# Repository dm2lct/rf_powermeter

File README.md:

# rf_powermeter
This is a try to build a rf powermeter for vhf and uhf frequencies. 
It should work with any directional coupler you attach on it. 
Currently I'm still working on it so it should not be rebuilt. 
When I have built and programmed it I will update this repository with the software. 
 
a vhf/uhf swr/powermeter

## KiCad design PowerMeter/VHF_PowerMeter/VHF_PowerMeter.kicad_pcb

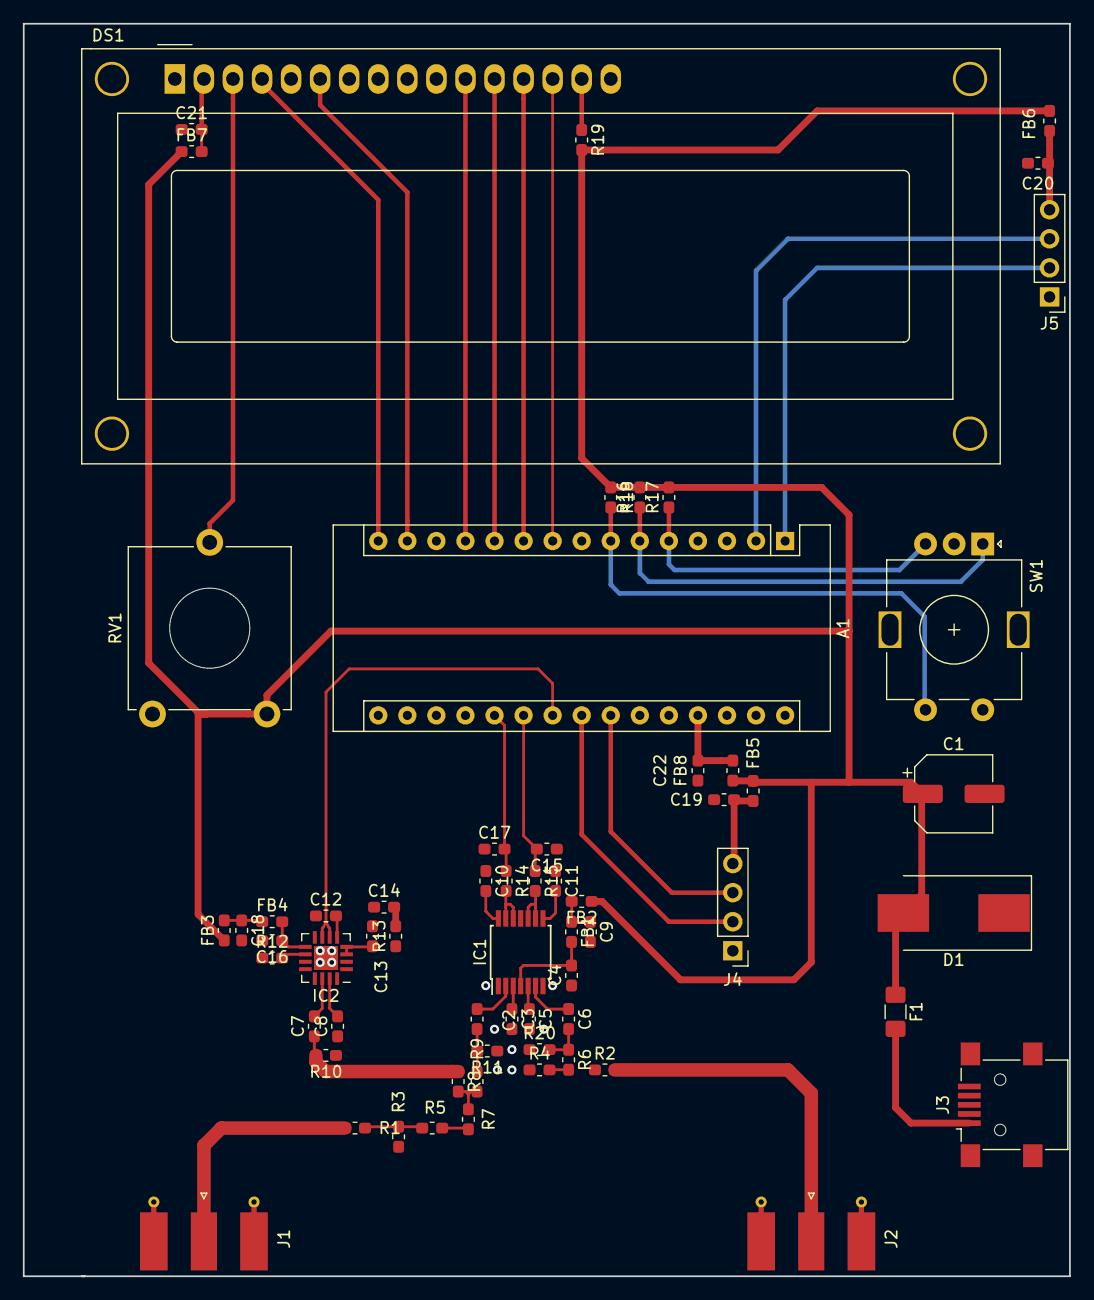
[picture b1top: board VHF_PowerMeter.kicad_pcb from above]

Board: 2 copper layers, 91.4 x 109.5 mm, 63 parts (0 on the bottom side), 53 nets.

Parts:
A1: Arduino_Nano_v3.x; Arduino_Nano
C1: CP1_Small; CP_Elec_6.3x7.7
C2, C3, C5: 1n; C_0603_1608Metric_Pad1.05x0.95mm_HandSolder
C4: 100nF; C_0603_1608Metric_Pad1.05x0.95mm_HandSolder
C6, C7, C8, C9, C10, C11, C12, C13, C14, C15, C16, C17, C18, C19, C20, C21, C22: C_Small; C_0603_1608Metric_Pad1.05x0.95mm_HandSolder
D1: DIODE; D_SMC_Handsoldering
DS1: WC1602A
F1: Polyfuse; Fuse_1206_3216Metric_Pad1.42x1.75mm_HandSolder
FB1, FB2, FB3, FB4, FB5, FB6, FB7, FB8: Ferrite_Bead_Small; L_0603_1608Metric_Pad1.05x0.95mm_HandSolder
IC1: AD8302ARUZ; TSSOP-14_4.4x5mm_P0.65mm
IC2: AD8318ACPZ-REEL7; LFCSP-16-1EP_4x4mm_P0.65mm_EP2.1x2.1mm
J1, J2: Conn_Coaxial; SMA_Molex_73251-1153_EdgeMount_Horizontal
J3: USB_B_Mini; USB_Mini-B_Lumberg_2486_01_Horizontal
J4, J5: Conn_01x04_Male; PinHeader_1x04_P2.54mm_Vertical
R1, R2, R3, R4, R5, R6, R12, R13, R14, R15, R16, R17, R18, R19: R_Small; R_0603_1608Metric_Pad1.05x0.95mm_HandSolder
R7, R8, R9: 16,67; R_0603_1608Metric_Pad1.05x0.95mm_HandSolder
R10, R11, R20: 50; R_0603_1608Metric_Pad1.05x0.95mm_HandSolder
RV1: R_POT; Potentiometer_ACP_CA14V-15_Vertical_Hole
SW1: Rotary_Encoder_Switch; RotaryEncoder_Alps_EC11E-Switch_Vertical_H20mm

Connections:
GND: A1.4, A1.29, C1.2, C3.2, C4.1, C5.2, C8.1, C9.2, C10.1, C11.1, C12.1, C13.1, C14.1, C15.1, C16.2, C17.1, C18.2, C19.2, C20.2, C21.1, C22.2, D1.1, DS1.1, DS1.5, DS1.16, IC1.1, IC1.7, IC2.1, IC2.2, IC2.8, IC2.11, IC2.12, IC2.17, J1.2, J2.2, J3.5, J3.6, J4.1, J5.1, R3.1, R4.1, R10.1, R11.1, R12.1, R20.1, RV1.3, SW1.C, SW1.S2
unnamed: A1.1, J5.2
unnamed: A1.2, J5.3
unnamed: A1.5, R17.1, SW1.B
unnamed: A1.6, R16.1, SW1.A
unnamed: A1.7, R18.2, SW1.S1
unnamed: A1.9, DS1.14
unnamed: A1.10, DS1.13
unnamed: A1.11, DS1.12
unnamed: A1.12, DS1.11
unnamed: A1.14, DS1.6
unnamed: A1.15, DS1.4
unnamed: A1.18, IC1.11
unnamed: A1.20, C17.2, R14.1
unnamed: A1.21, C15.2, R15.1
unnamed: A1.22, IC2.6, IC2.7
unnamed: A1.23, J4.2
unnamed: A1.24, J4.3
unnamed: A1.27, C22.1, FB8.2
unnamed: C2.1, IC1.2
unnamed: C2.2, R9.2, R11.2
unnamed: C3.1, IC1.3
unnamed: C4.2, FB1.2, IC1.4
unnamed: C5.1, IC1.5
unnamed: C6.1, IC1.6
unnamed: C6.2, R6.1, R20.2
unnamed: C7.1, R8.1, R10.2
unnamed: C7.2, IC2.14
unnamed: C8.2, IC2.15
unnamed: C9.1, FB1.1, FB2.2
unnamed: C10.2, IC1.14
unnamed: C11.2, IC1.8
unnamed: C12.2, IC2.5
unnamed: C13.2, IC2.3, IC2.4, IC2.16, R13.1
unnamed: C16.1, FB4.2, IC2.9
unnamed: C18.1, FB3.2, FB4.1
unnamed: C19.1, FB5.2, J4.4
unnamed: C20.1, FB6.2, J5.4
unnamed: C21.2, DS1.2, FB7.2
unnamed: DS1.3, RV1.2
unnamed: DS1.15, R19.1
unnamed: F1.2, J3.1
unnamed: IC1.9, IC1.10, R15.2
unnamed: IC1.12, IC1.13, R14.2
unnamed: IC2.10, R12.2
unnamed: J1.1, R1.2
unnamed: J2.1, R2.2
unnamed: J3.2, J3.3
unnamed: R1.1, R3.2, R5.2
unnamed: R2.1, R4.2, R6.2
unnamed: R5.1, R7.1
unnamed: R7.2, R8.2, R9.1
VCC: C1.1, C14.2, D1.2, F1.1, FB2.1, FB3.1, FB5.1, FB6.1, FB7.1, FB8.1, R13.2, R16.2, R17.2, R18.1, R19.2, RV1.1

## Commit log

2019-01-22 Readme hinzugefügt
